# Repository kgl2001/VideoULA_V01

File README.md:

# VideoULA V01 — BBC Micro Video ULA Replacement
## 44-pin Xilinx XC9572XL CPLD Version

This repository contains the hardware design and firmware for the VideoULA V01, a drop-in replacement for the VC2069 Video ULA (IC6) in the Acorn BBC Micro Model B.

---

## Project Overview

The original BBC Micro Video ULA (IC6) is a custom ASIC that is no longer manufactured. Failed or missing ULAs result in a non-functional machine. This project provides a modern replacement using a CPLD and a small external SRAM for palette storage.

There are three hardware versions of this replacement, each in a separate repository:

| Version | CPLD | Macrocells | Tool | Repository |
|---|---|---|---|---|
| **V01** | Xilinx XC9572XL-10-VQ44 | 72 | ISE 14.7 | This repo |
| V02 | Xilinx XC9572XL-10-VQ64 | 72 | ISE 14.7 | [VideoULA_V02](https://github.com/kgl2001/VideoULA_V02) |
| V03 | Atmel ATF1504AS-10AU44 | 64 | Quartus 13.0 SP1 | [VideoULA_V03](https://github.com/kgl2001/VideoULA_V03) |

All three versions share the same 28-pin DIP footprint as the original ULA and are pin-compatible with the BBC Micro motherboard.

---

## V01 Hardware

- **CPLD**: Xilinx XC9572XL-10-VQ44 (72 macrocells, 3.3V core, 5V tolerant I/O)
- **SRAM**: ISSI IS62C256AL-45TLI (32K×8, 5V, TSOP-28, 45ns) — only locations 0-15 and bits 0-3 used
- **Oscillator**: 48MHz SMD oscillator (3225 package, 5V) — for 48MHz operating mode only
- **LDO**: XC6206P332MR (SOT-23, 3.3V) — powers CPLD core

### Hardware Revisions

| Revision | Status | Changes |
|---|---|---|
| Rev01 | Built and tested | Initial release |
| Rev02 | PCB designed, not yet built | Added 47Ω series resistor and 74LVC1G17 Schmitt trigger buffer on CLK_IN; CPLD pin assignments updated |
| Rev03 | PCB designed, not yet built | Added 74LV6T17 to buffer all clock outputs (8/4/2/1MHz, CRTC) for Master 128 compatibility |
| Rev04 | PCB designed, not yet built | Repositioned JTAG header |

Note: Only Rev01 has been built and tested. Rev02 onwards incorporate improvements identified during Rev01 testing. The latest revision supersedes the earlier ones, which are kept for the historical record.

### CLK_IN Reliability Daughterboard

During testing of Rev01 on BBC Micro machines with the original 16MHz clock circuit, some machines showed reliability issues in 16MHz operating mode — particularly on cold startup. Investigation revealed that the BBC's 16MHz crystal oscillator circuit produces a noisy clock signal that the CPLD occasionally misinterprets as spurious edges, causing display glitches.

To address this without waiting for a new PCB revision, a small standalone buffer board was developed. This daughterboard:

- Plugs into the BBC Micro motherboard in place of the VideoULA V01
- The VideoULA V01 then plugs into the daughterboard
- Intercepts the 16MHz clock signal from the BBC motherboard
- Passes it through a 47Ω series resistor and 74HCT14E Schmitt trigger buffer before it reaches the CPLD
- Passes all other signals through unchanged

The 74HCT14E was chosen as a through-hole part for ease of hand soldering. Rev02+ PCB designs use the smaller surface-mount 74LVC1G17 in conjunction with a series resistor to achieve the same signal conditioning in a more compact form.

This fix was confirmed to resolve the cold startup reliability issues on affected machines. The improvement has been incorporated into Rev02 of the V01 PCB and all subsequent hardware versions.

The daughterboard design files are included in this repository.

---

## Firmware

The firmware is written in Verilog and built using Xilinx ISE 14.7.

### Operating Modes

Two firmware builds are required — one per operating mode. To switch modes, reprogram the CPLD with the appropriate `.jed` file. A solder bridge on the PCB selects whether the 48MHz oscillator or the BBC's 16MHz clock is connected to the CPLD clock input.

#### 48MHz Mode (recommended)
- Uses the onboard 48MHz oscillator as the master clock
- Generates all BBC clock outputs (8/4/2/1MHz, CRTC, 6MHz) internally
- Provides clean, phase-locked 6MHz output for the SAA5050 teletext chip (tD ≈ 20ns ✓)
- Works reliably on all machines from cold power-up, including those with noisy clock circuits
- Build: uncomment `` `define CLK_48MHZ `` in `VideoULA.v`

#### 16MHz Mode
- Uses the BBC motherboard's 16MHz clock as the master clock
- No onboard oscillator required
- May show brief display noise on cold startup on machines with noisy 16MHz clock circuits
- The CLK_IN daughterboard resolves this on Rev01; Rev02+ has the fix built in
- The CPLD generates a phase-locked 6MHz from the 16MHz clock (small fixed jitter, about 10ns); the motherboard's own 6MHz can be used instead
- Build: uncomment `` `define CLK_16MHZ `` in `VideoULA.v`

#### CLK_AUTO (experimental)
- A third option, for the unified Rev02 to Rev04 boards, where the mode is read at power-up from the `SRAM_nWE` pin (JP2). One build covers both clocks
- Only tested on Rev01 hardware. It fits with no headroom (70 to 72 of 72 macrocells), and because the strap is read at power-up it may occasionally pick the wrong mode; power-cycle to recover
- The fixed 48MHz and 16MHz builds are smaller and have had more testing
- Build: uncomment `` `define CLK_AUTO `` (and comment out `CLK_48MHZ`) in `VideoULA.v`

### ISE Fitter Settings (critical)

| Setting | Value | Notes |
|---|---|---|
| Implementation Template | **Optimise Speed** | Density causes timing failures at temperature |
| Macrocell Power | **Std** | Low Power prevents BBC from booting |
| Output Slew Rate | Fast | |
| Default Powerup Value | Low | |
| Pterms | **14** (16MHz build only) | Default 25 causes silent fit failure in 16MHz build |

### Build Instructions

1. Open Xilinx ISE 14.7
2. Create a new project targeting `XC9572XL-10-VQ44`
3. Add `src/VideoULA.v` and `src/VideoULA.ucf` to the project
4. Select the operating mode by uncommenting the appropriate `define` in `VideoULA.v`
5. Set fitter options as above
6. Run `Implement Design` to generate the `.jed` file
7. Program the CPLD using iMPACT or a compatible JTAG programmer

---

## SRAM Wiring

The external SRAM stores the 16-entry colour palette (4 bits per entry):

| SRAM Pin | Connection |
|---|---|
| A0-A3 | CPLD SRAM_ADDR[0:3] |
| A4-A14 | GND (tie low) |
| D0-D3 | CPLD SRAM_DATA[0:3] (bidirectional) |
| D4-D7 | Leave unconnected |
| /WE | CPLD SRAM_nWE |
| /OE | GND (always output enabled) |
| /CS | GND (always selected) |

---

## 6MHz Clock for Mode 7 (Teletext)

The SAA5050 teletext chip requires a 6MHz clock with a specific phase relationship to the 1MHz system clock (tD = 6-60ns from 6MHz rising edge to 1MHz falling edge).

- **48MHz mode**: The CPLD generates a clean, phase-locked 6MHz output on the CLK_6M pin (tD ≈ 20ns ✓). This can be connected to the SAA5050 using a small replacement board for IC37 (Model B) or IC25 (Master) - see the [6MHz Interface Boards](https://github.com/kgl2001/VideoULA_V01/tree/main/KiCAD%20Files/6MHz%20Interface%20Boards).
- **16MHz mode**: The CPLD also generates a 6MHz output on CLK_6M, derived from the 16MHz clock and phase-locked to the 1MHz (tD ≈ 31ns ✓). It has a small fixed jitter (about 10ns), so M7CALIB can show slightly more noise. If CLK_6M is not connected, the BBC motherboard's existing 6MHz circuit is used as normal.

The CPLD's CLK_6M output is brought out on a single-pin header on the V01 board, marked **6MHz Clk** on the silkscreen (J2 in the schematic). To use the CPLD's 6MHz in either the 48MHz or the 16MHz build, connect it to the pin marked **6MHz** on the IC37 / IC25 interface board (J1 pin 1 in the schematic; the other pin, marked HSyn, is not used), or to the teletext IC's 6MHz input with a clip lead as described above. If it is left unconnected, the motherboard's own 6MHz is used as normal.

With the motherboard's own 6MHz circuit, the mode 7 cursor on a Master 128 is half a pixel (one column) to the left. The full Master 128 results are in the [CPLD README](CPLD%20Files/README.md#master-128-results-v01-rev01).

---

## PCB Design Notes

The PCB has been designed using KiCAD V10 as a 2-layer board. It can easily be changed to a 4-layer board with GND/Power planes on the inner layers if signal integrity is a concern.

### JLCPCB Fabrication

The board design includes a 5×5mm silkscreen box on the underside of the PCB. This is used by JLCPCB to position a QR code serial number. When ordering from JLCPCB:

- Select **Specify position** in the QR code / 2D barcode options during the ordering process
- If this option is not selected, JLCPCB will print the 5×5mm silkscreen box as-is and attempt to place the QR code at a different location of their choosing

If not using JLCPCB, the chosen fabricator will likely print the 5×5mm box as a plain white square on the PCB. To avoid this, remove the silkscreen box from the PCB design and regenerate the Gerber files before submitting.

### Assembly

A combined CPL (Component Placement List) and BOM (Bill of Materials) Excel file is included in the Gerbers folder. This can be used directly with the JLCPCB PCBA (PCB Assembly) service.

Note that the JLCPCB Economy PCBA process only assembles components on one side of the PCB. Select the **top side** for assembly — this leaves only the SRAM and its associated decoupling capacitor to be hand soldered to the underside of the board.

---

## Known Limitations

- **Cold startup noise (16MHz mode, standard clock machines)**: Machines with noisy 16MHz clock circuits may show brief display noise on cold power-up. Use the CLK_IN daughterboard (Rev01) or upgrade to Rev02+ which has the fix built in. The 48MHz operating mode is not affected.
- **Master 128 compatibility**: Rev01 has been tested on a Master 128 in both builds (see the [CPLD README](CPLD%20Files/README.md#master-128-results-v01-rev01)). Clock output buffering (added in Rev03) may still be required for full Master 128 compatibility on some machines.
- **SCART/HDMI adapter compatibility**: Some SCART→HDMI display adapters may show minor pixel artefacts with non-standard screen modes. RGBtoHDMI and direct CRT connections are not affected.

---

## Compatibility

Tested on BBC Micro Model B with original clock circuit and with clock fixer modification, and on a BBC Master 128 (Rev01).

---

## Credits

- **Ken Lowe** — PCB design, Verilog development and testing
- **hoglet (Stardot forums)** — Clock architecture analysis, DRAM timing analysis, SRAM write address setup analysis and proposed fix, community testing
- **radiofan (Stardot forums)** — SRAM write fix, 16MHz-derived 6MHz clock approach
- **Stardot community** — Testing, feedback and suggestions

---

## Licence

Hardware: [Creative Commons BY-SA 4.0](https://creativecommons.org/licenses/by-sa/4.0/)

Firmware: [MIT Licence](https://opensource.org/licenses/MIT)

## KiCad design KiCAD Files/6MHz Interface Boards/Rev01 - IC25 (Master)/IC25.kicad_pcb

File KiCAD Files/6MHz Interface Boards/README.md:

# 6MHz Interface Boards

Two small drop-in replacement boards that let the VideoULA CPLD supply the 6MHz clock to the SAA5050 teletext chip on a BBC Micro.

| Board | Fits | Replaces | Folder |
|---|---|---|---|
| IC37 board | BBC Model B | IC37 (74LS04) | [Rev01 - IC37 (Model B)](Rev01%20-%20IC37%20(Model%20B)) |
| IC25 board | BBC Master 128 | IC25 (74LS86) | [Rev01 - IC25 (Master)](Rev01%20-%20IC25%20(Master)) |

## Why these boards exist

In 48MHz mode the CPLD generates a clean 6MHz clock, phase-locked to the other video clocks (CLK_6M). Mode 7 gives its cleanest picture, and a correctly aligned cursor on both Model B and Master, when that clock is fed to the teletext IC instead of the motherboard's own 6MHz circuit.

The motherboard generates its 6MHz in the last gate of IC37 (Model B, pin 8) or IC25 (Master, pin 11). Each board replaces the original chip with a socketed 74HCT part, and lets you disconnect that final gate from the motherboard's 6MHz line and drive the line from the CPLD instead.

The boards are only needed to use the CPLD's CLK_6M. Without them the motherboard's own 6MHz circuit is used, as normal.

## Parts

The originals are 74LS parts, so the boards use **74HCT** parts, which run from 5V with TTL-compatible inputs. Do not substitute 3.3V logic (74LVC and similar).

| Board | Part | Package | JLCPCB |
|---|---|---|---|
| IC37 | 74HCT04 | TSSOP-14 | C131317 |
| IC25 | 74HCT86 | TSSOP-14 | C842458 |
| IC37 | 100nF decoupling capacitor (C37) | 0603 | C14663 |
| IC25 | 100nF decoupling capacitor (C25) | 0603 | C14663 |

The JLCPCB BOM covers only the SMD parts (the HCT chip and the capacitor). The through-hole parts are **not** in the BOM and must be fitted by hand:

- Two 7-pin round (machined) pin headers, soldered into the board's DIP pin positions. These plug into the motherboard socket.
- The 2-pin right-angle header J1, on the underside.

## Solder bridge settings

Both boards (IC37 and IC25) have two 3-pad solder bridges, JP1 and JP2, on the underside of the PCB, with identical settings. They are bridged 1-2 as shipped (the default). To change position, cut the thin track between pads 1 and 2 and bridge the pads you want with solder.

| Setting | JP1 | JP2 |
|---|---|---|
| **VideoULA 6MHz (default)**: CPLD drives the 6MHz line | bridge 1-2 | bridge 1-2 |
| **Inverted VideoULA 6MHz**: CPLD clock, inverted by the on-board gate | bridge 1-2 | bridge 2-3 |
| **Original 6MHz**: the motherboard's own circuit, as if the original chip were fitted | bridge 2-3 | bridge 2-3 |

For the default, the on-board gate is disconnected from the motherboard, and its input is tied to the CPLD clock so it does not float.

On the IC25 board the gate is an XOR with one input tied to 5V on the Master motherboard, so it acts as an inverter, just as the IC37 gate does.

## Connecting the CPLD

J1 is a 2-pin right-angle header fitted on the underside of the PCB. The labels are printed on the top silkscreen:

| J1 pin | Label | Use |
|---|---|---|
| 1 | 6MHz | Connect to the CPLD ULA's CLK_6M output |
| 2 | HSync | Added to aid testing; not needed in operation. Leave unconnected. (Silkscreen reads "HSyn" as there was no room for the full name.) |

## Fitting

1. Desolder the original chip (IC37 on a Model B, IC25 on a Master) from the motherboard, and fit a 14-pin DIP socket in its place. Note the orientation (pin 1).
2. Solder the round pin headers to the board, then plug the board into the socket, pin 1 matching.
3. Check the solder bridges (default is the VideoULA 6MHz).
4. Connect J1 to the CPLD ULA's CLK_6M.
5. Build the CPLD in either the 48MHz or the 16MHz mode (see the firmware READMEs).

### Without removing the chip

If you would rather not remove IC37 / IC25, you can cut the output leg of the gate that drives the 6MHz signal (pin 8 of IC37 on a Model B, pin 11 of IC25 on a Master) and connect the CPLD's CLK_6M to the teletext IC's 6MHz input with a clip lead (pin 19 of IC5 on a Model B, pin 19 of IC32 on a Master). Cutting the leg is a permanent modification to the chip.

## Status

Rev 01 has been built and tested in both the IC37 (Model B) and IC25 (Master) versions, on a Model B and a Master 128.

The 48MHz build gives the cleanest 6MHz. The 16MHz build now also works with the CPLD's 6MHz: it is generated from the 16MHz clock and phase-locked to the 1MHz clock. It has a small fixed jitter (about 10ns), so M7CALIB can show slightly more noise than in the 48MHz build. (An earlier 16MHz build generated the 6MHz from the 48MHz oscillator and could not be phase-locked to the 16MHz clock.)

## Files

Each folder is a KiCAD project (KiCAD 10) with schematic, PCB, a `3DModels` folder, and `Gerbers` for JLCPCB fabrication. The 3D model path is relative to the project, so keep the folder structure intact.

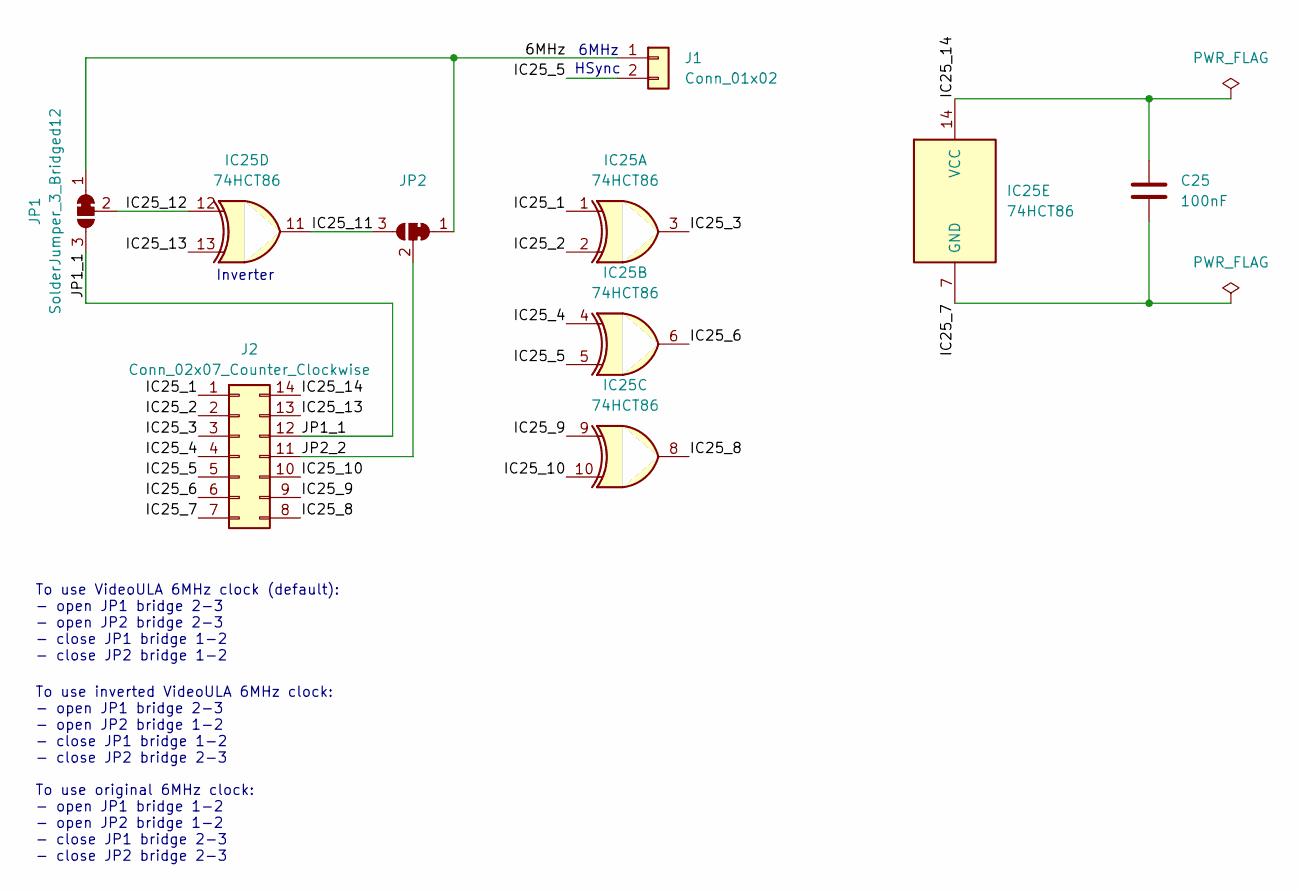
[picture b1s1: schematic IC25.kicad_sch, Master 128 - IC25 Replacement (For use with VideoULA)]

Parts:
C25: 100nF; C_0603_1608Metric
IC25: 74HCT86; TSSOP-14_4.4x5mm_P0.65mm
J1: Conn_01x02; PinHeader_1x02_P2.54mm_Horizontal
J2: Conn_02x07_Counter_Clockwise; DIP-14_W7.62mm
JP1, JP2: SolderJumper_3_Bridged12; SolderJumper-3_P1.3mm_Bridged12_RoundedPad1.0x1.5mm

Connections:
/6MHz: J1.1, JP1.1 (A), JP2.1 (A)
/IC25_1: IC25.1, J2.1
/IC25_2: IC25.2, J2.2
/IC25_3: IC25.3, J2.3
/IC25_4: IC25.4, J2.4
/IC25_5: IC25.5, J1.2, J2.5
/IC25_6: IC25.6, J2.6
/IC25_7: C25.2, IC25.7 (GND), J2.7
/IC25_8: IC25.8, J2.8
/IC25_9: IC25.9, J2.9
/IC25_10: IC25.10, J2.10
/IC25_11: IC25.11, JP2.3 (B)
/IC25_12: IC25.12, JP1.2 (C)
/IC25_13: IC25.13, J2.13
/IC25_14: C25.1, IC25.14 (VCC), J2.14
/JP1_1: J2.12, JP1.3 (B)
/JP2_2: J2.11, JP2.2 (C)

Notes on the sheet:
HSync
To use VideoULA 6MHz clock (default): - open JP1 bridge 2-3 - open JP2 bridge 2-3 - close JP1 bridge 1-2 - close JP2 bridge 1-2
To use inverted VideoULA 6MHz clock: - open JP1 bridge 2-3 - open JP2 bridge 1-2 - close JP1 bridge 1-2 - close JP2 bridge 2-3
6MHz
Inverter
To use original 6MHz clock: - open JP1 bridge 1-2 - open JP2 bridge 1-2 - close JP1 bridge 2-3 - close JP2 bridge 2-3

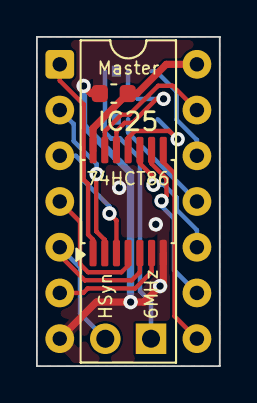
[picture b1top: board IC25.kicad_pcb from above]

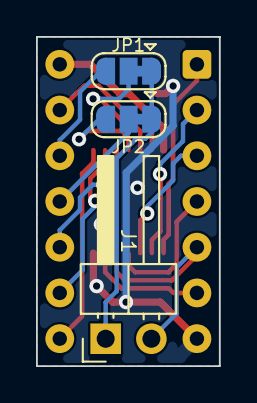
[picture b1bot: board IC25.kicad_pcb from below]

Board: 2 copper layers, 10.2 x 18.3 mm, 6 parts (3 on the bottom side), 17 nets.

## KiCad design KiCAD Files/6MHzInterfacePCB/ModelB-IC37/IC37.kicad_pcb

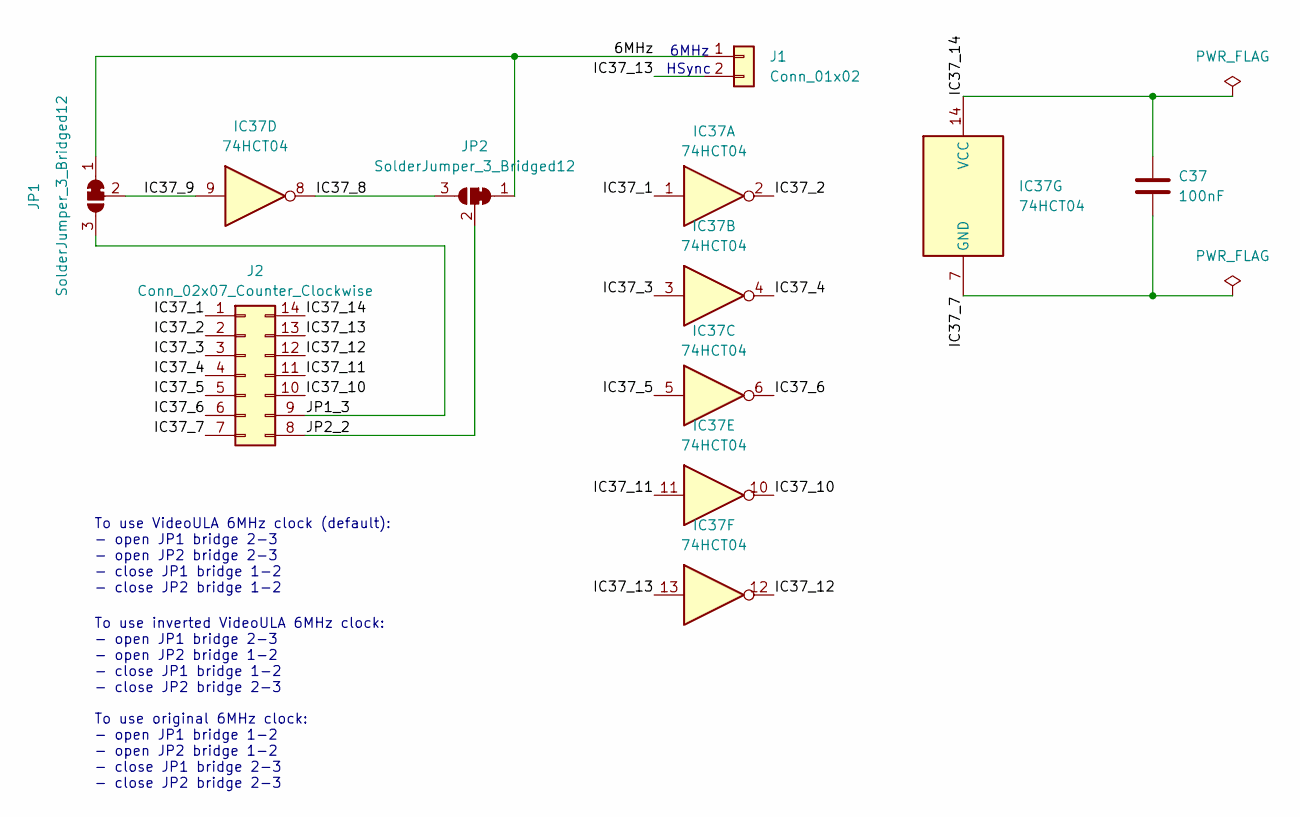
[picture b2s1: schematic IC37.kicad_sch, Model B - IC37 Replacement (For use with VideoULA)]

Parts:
C37: 100nF; C_0603_1608Metric
IC37: 74HCT04; TSSOP-14_4.4x5mm_P0.65mm
J1: Conn_01x02; PinHeader_1x02_P2.54mm_Horizontal
J2: Conn_02x07_Counter_Clockwise; DIP-14_W7.62mm
JP1, JP2: SolderJumper_3_Bridged12; SolderJumper-3_P1.3mm_Bridged12_RoundedPad1.0x1.5mm

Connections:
/6MHz: J1.1, JP1.1 (A), JP2.1 (A)
/IC37_1: IC37.1, J2.1
/IC37_2: IC37.2, J2.2
/IC37_3: IC37.3, J2.3
/IC37_4: IC37.4, J2.4
/IC37_5: IC37.5, J2.5
/IC37_6: IC37.6, J2.6
/IC37_7: C37.2, IC37.7 (GND), J2.7
/IC37_8: IC37.8, JP2.3 (B)
/IC37_9: IC37.9, JP1.2 (C)
/IC37_10: IC37.10, J2.10
/IC37_11: IC37.11, J2.11
/IC37_12: IC37.12, J2.12
/IC37_13: IC37.13, J1.2, J2.13
/IC37_14: C37.1, IC37.14 (VCC), J2.14
/JP1_3: J2.9, JP1.3 (B)
/JP2_2: J2.8, JP2.2 (C)

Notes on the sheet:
HSync
To use inverted VideoULA 6MHz clock: - open JP1 bridge 2-3 - open JP2 bridge 1-2 - close JP1 bridge 1-2 - close JP2 bridge 2-3
6MHz
To use original 6MHz clock: - open JP1 bridge 1-2 - open JP2 bridge 1-2 - close JP1 bridge 2-3 - close JP2 bridge 2-3
To use VideoULA 6MHz clock (default): - open JP1 bridge 2-3 - open JP2 bridge 2-3 - close JP1 bridge 1-2 - close JP2 bridge 1-2

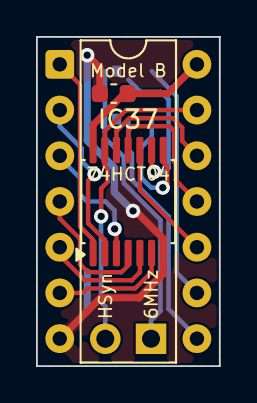
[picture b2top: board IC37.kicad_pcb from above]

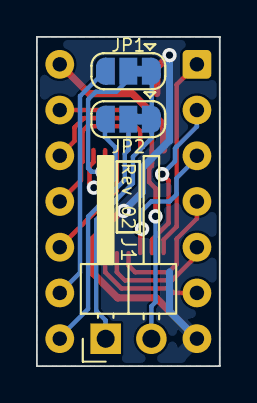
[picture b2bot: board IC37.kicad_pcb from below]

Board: 2 copper layers, 10.2 x 18.3 mm, 6 parts (3 on the bottom side), 17 nets.

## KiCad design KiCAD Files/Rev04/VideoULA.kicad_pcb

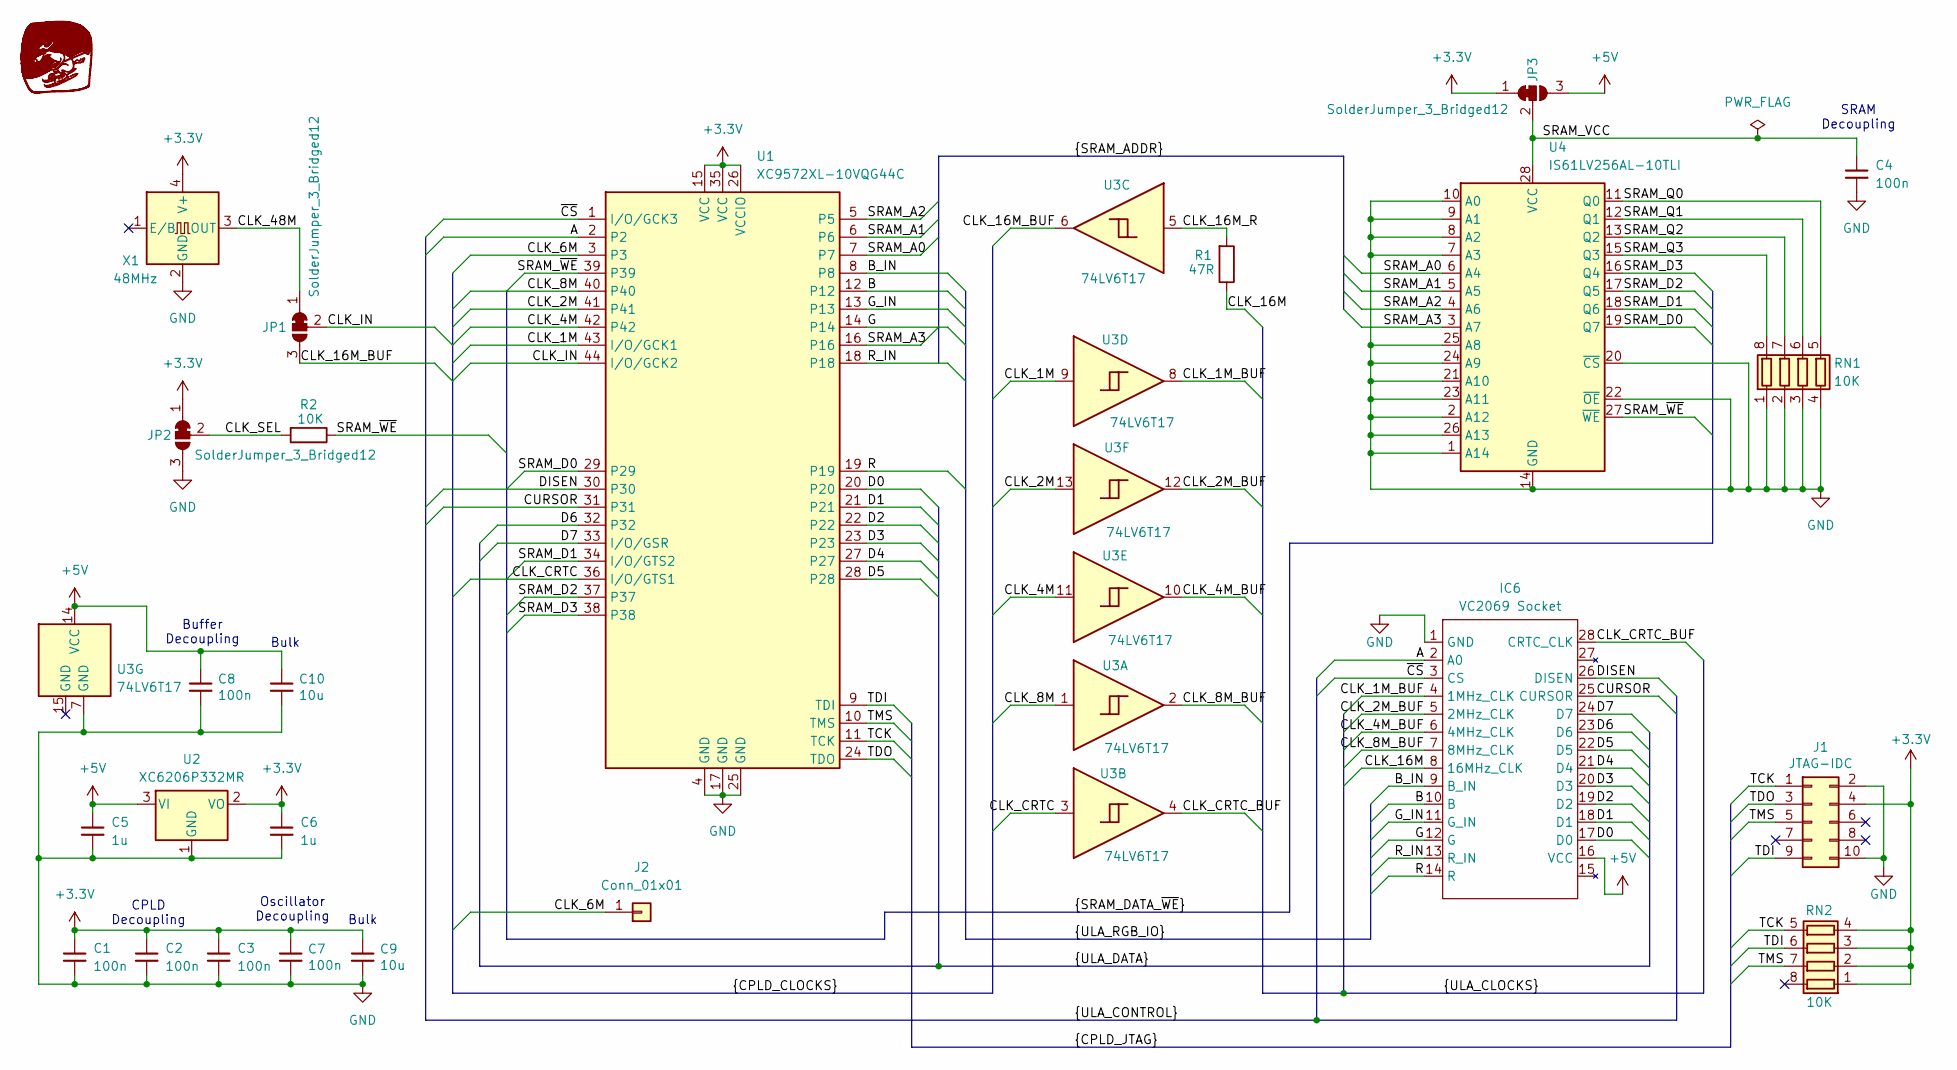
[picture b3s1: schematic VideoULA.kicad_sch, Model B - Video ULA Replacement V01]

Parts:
C1, C2, C3, C4, C7, C8: 100n; C_0603_1608Metric; JLC Part Number C14663
C5, C6: 1u; C_0603_1608Metric; JLC Part Number C15849
C9, C10: 10u; C_0603_1608Metric; JLC Part Number C19702
G1: Skidog; skidog_inv
IC6: VC2069 Socket; DIP-28_W15.24mm
J1: JTAG-IDC; PinHeader_2x05_P2.54mm_Vertical
J2: Conn_01x01; PinHeader_1x01_P2.54mm_Horizontal
JP1, JP2, JP3: SolderJumper_3_Bridged12; SolderJumper-3_P1.3mm_Bridged12_RoundedPad1.0x1.5mm
R1: 47R; R_0603_1608Metric; JLC Part Number C23182
R2: 10K; R_0603_1608Metric; JLC Part Number C25804
RN1, RN2: 10K; R_Array_Convex_4x0603; JLC Part Number C29718
U1: XC9572XL-10VQG44C; LQFP-44_10x10mm_P0.8mm; JLC Part Number C569042
U2: XC6206P332MR; SOT-23-3; JLC Part Number C5446
U3: 74LV6T17; DHWQFN-14-1EP_2.5x3mm_P0.5mm_EP1x1.5mm_ThermalVias; JLC Part Number C22428345
U4: IS61LV256AL-10TLI; TSOP-I-28_11.8x8mm_P0.55mm_SRAM; JLC Part Number C2062662
X1: 48MHz; Oscillator_SMD_Yajingxin_TFOM48M4RHKCNT2T-4Pin_3.2x2.5mm; JLC Part Number C454614

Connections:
+3.3V: C1.1, C2.1, C3.1, C6.1, C7.1, C9.1, J1.4, JP2.1 (A), JP3.1 (A), RN2.1 (R1.1), RN2.2 (R2.1), RN2.3 (R3.1), RN2.4 (R4.1), U1.15 (VCC), U1.26 (VCCIO), U1.35 (VCC), U2.2 (VO), X1.4 (V+)
+5V: C5.1, C8.1, C10.1, IC6.16 (VCC), JP3.3 (B), U2.3 (VI), U3.14 (VCC)
/A: IC6.2 (A0), U1.2
/B: IC6.10 (B), U1.12
/B_IN: IC6.9 (B_IN), U1.8
/CLK_1M: U1.43 (I/O/GCK1), U3.9
/CLK_1M_BUF: IC6.4 (1MHz_CLK), U3.8
/CLK_2M: U1.41, U3.13
/CLK_2M_BUF: IC6.5 (2MHz_CLK), U3.12
/CLK_4M: U1.42, U3.11
/CLK_4M_BUF: IC6.6 (4MHz_CLK), U3.10
/CLK_6M: J2.1 (Pin_1_1), U1.3
/CLK_8M: U1.40, U3.1
/CLK_8M_BUF: IC6.7 (8MHz_CLK), U3.2
/CLK_16M: IC6.8 (16MHz_CLK), R1.1
/CLK_16M_BUF: JP1.3 (B), U3.6
/CLK_16M_R: R1.2, U3.5
/CLK_48M: JP1.1 (A), X1.3 (OUT)
/CLK_CRTC: U1.36 (I/O/GTS1), U3.3
/CLK_CRTC_BUF: IC6.28 (CRTC_CLK), U3.4
/CLK_IN: JP1.2 (C), U1.44 (I/O/GCK2)
/CLK_SEL: JP2.2 (C), R2.2
/CURSOR: IC6.25 (CURSOR), U1.31
/D0: IC6.17 (D0), U1.20
/D1: IC6.18 (D1), U1.21
/D2: IC6.19 (D2), U1.22
/D3: IC6.20 (D3), U1.23
/D4: IC6.21 (D4), U1.27
/D5: IC6.22 (D5), U1.28
/D6: IC6.23 (D6), U1.32
/D7: IC6.24 (D7), U1.33 (I/O/GSR)
/DISEN: IC6.26 (DISEN), U1.30
/G: IC6.12 (G), U1.14
/G_IN: IC6.11 (G_IN), U1.13
/R: IC6.14 (R), U1.19
/R_IN: IC6.13 (R_IN), U1.18
/SRAM_A0: U1.7, U4.6 (A4)
/SRAM_A1: U1.6, U4.5 (A5)
/SRAM_A2: U1.5, U4.4 (A6)
/SRAM_A3: U1.16, U4.3 (A7)
/SRAM_D0: U1.29, U4.19 (Q7)
/SRAM_D1: U1.34 (I/O/GTS2), U4.18 (Q6)
/SRAM_D2: U1.37, U4.17 (Q5)
/SRAM_D3: U1.38, U4.16 (Q4)
/SRAM_Q0: RN1.5 (R4.2), U4.11 (Q0)
/SRAM_Q1: RN1.6 (R3.2), U4.12 (Q1)
/SRAM_Q2: RN1.7 (R2.2), U4.13 (Q2)
/SRAM_Q3: RN1.8 (R1.2), U4.15 (Q3)
/SRAM_VCC: C4.1, JP3.2 (C), U4.28 (VCC)
/SRAM_~WE: R2.1, U1.39, U4.27 (~WE)
/TCK: J1.1, RN2.5 (R4.2), U1.11 (TCK)
/TDI: J1.9, RN2.6 (R3.2), U1.9 (TDI)
/TDO: J1.3, U1.24 (TDO)
/TMS: J1.5, RN2.7 (R2.2), U1.10 (TMS)
/~CS: IC6.3 (CS), U1.1 (I/O/GCK3)
GND: C1.2, C2.2, C3.2, C4.2, C5.2, C6.2, C7.2, C8.2, C9.2, C10.2, IC6.1 (GND), J1.2, J1.10, JP2.3 (B), RN1.1 (R1.1), RN1.2 (R2.1), RN1.3 (R3.1), RN1.4 (R4.1), U1.4 (GND), U1.17 (GND), U1.25 (GND), U2.1 (GND), U3.7 (GND), U4.1 (A14), U4.2 (A12), U4.7 (A3), U4.8 (A2), U4.9 (A1), U4.10 (A0), U4.14 (GND), U4.20 (~CS), U4.21 (A10), U4.22 (~OE), U4.23 (A11), U4.24 (A9), U4.25 (A8), U4.26 (A13), X1.2 (GND)

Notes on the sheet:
SRAM Decoupling
Oscillator Decoupling
CPLD Decoupling
Bulk
Buffer Decoupling

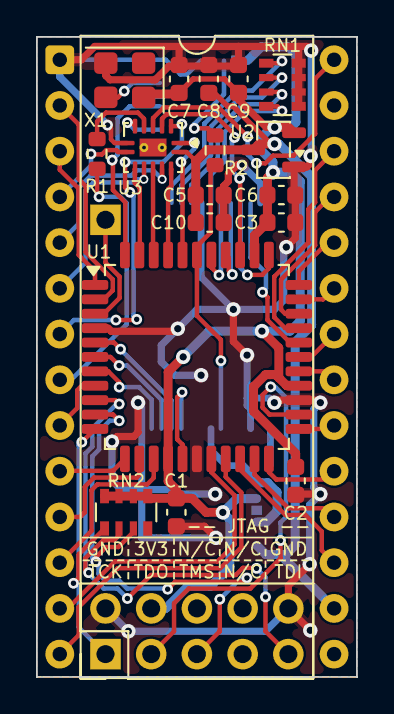
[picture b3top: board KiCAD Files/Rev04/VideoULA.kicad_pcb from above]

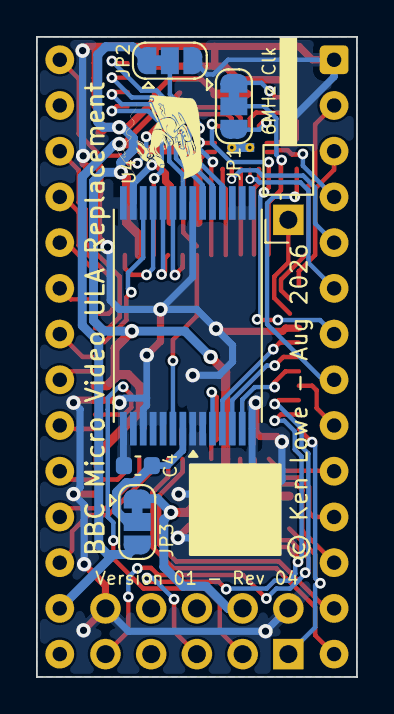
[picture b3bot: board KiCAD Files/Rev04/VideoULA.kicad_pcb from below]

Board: 2 copper layers, 17.8 x 35.6 mm, 26 parts (7 on the bottom side), 56 nets.

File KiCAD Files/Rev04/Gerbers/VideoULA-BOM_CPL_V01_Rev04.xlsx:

Designator | Val | Package | Mid X | Mid Y | Rotation | Layer | JLC Part Number
C4 | 100n | C_0603_1608Metric | 88.882531999999998 | -62.421548000000001 | 0 | bottom | C14663
U4 | IS61LV256AL-10TLI | TSOP-I-28_11.8x8mm_P0.55mm_SRAM | 86.111000000000004 | -54.097000000000001 | 90 | bottom | C2062662
C1 | 100n | C_0603_1608Metric | 84.46 | -65.013999999999996 | -90 | top | C14663
C2 | 100n | C_0603_1608Metric | 91.089731999999998 | -63.266348000000001 | -90 | top | C14663
C3 | 100n | C_0603_1608Metric | 90.293999999999997 | -48.915399999999998 | 0 | top | C14663
C5 | 1u | C_0603_1608Metric | 86.3142 | -47.391399999999997 | 0 | top | C15849
C6 | 1u | C_0603_1608Metric | 90.293999999999997 | -47.391399999999997 | 0 | top | C15849
C7 | 100n | C_0603_1608Metric | 84.612399999999994 | -40.939799999999998 | 90 | top | C14663
C8 | 100n | C_0603_1608Metric | 86.2624 | -40.939799999999998 | 90 | top | C14663
C9 | 10u | C_0603_1608Metric | 87.912400000000005 | -40.939799999999998 | 90 | top | C19702
C10 | 10u | C_0603_1608Metric | 86.3142 | -48.915399999999998 | 0 | top | C19702
R1 | 47R | R_0603_1608Metric | 80.0578 | -45.105400000000003 | 90 | top | C23182
R2 | 10K | R_0603_1608Metric | 86.611000000000004 | -44.902200000000001 | 90 | top | C25804
RN1 | 10K | R_Array_Convex_4x0603 | 90.355732000000003 | -41.263348000000001 | -90 | top | C29718
RN2 | 10K | R_Array_Convex_4x0603 | 81.672399999999996 | -65.013999999999996 | 0 | top | C29718
U1 | XC9572XL-10VQG44C | LQFP-44_10x10mm_P0.8mm | 85.602999999999994 | -56.383000000000003 | -90 | top | C569042
U2 | XC6206P332MR | SOT-23-3 | 89.862200000000001 | -44.876800000000003 | 0 | top | C5446
U3 | 74LV6T17 | DHWQFN-14-1EP_2.5x3mm_P0.5mm_EP1x1.5mm_ThermalVias | 83.164599999999993 | -44.7498 | -90 | top | C22428345
X1 | 48MHz | Oscillator_SMD_Yajingxin_TFOM48M4RHKCNT2T-4Pin_3.2x2.5mm | 81.592731999999998 | -41.009348000000003 | 180 | top | C454614

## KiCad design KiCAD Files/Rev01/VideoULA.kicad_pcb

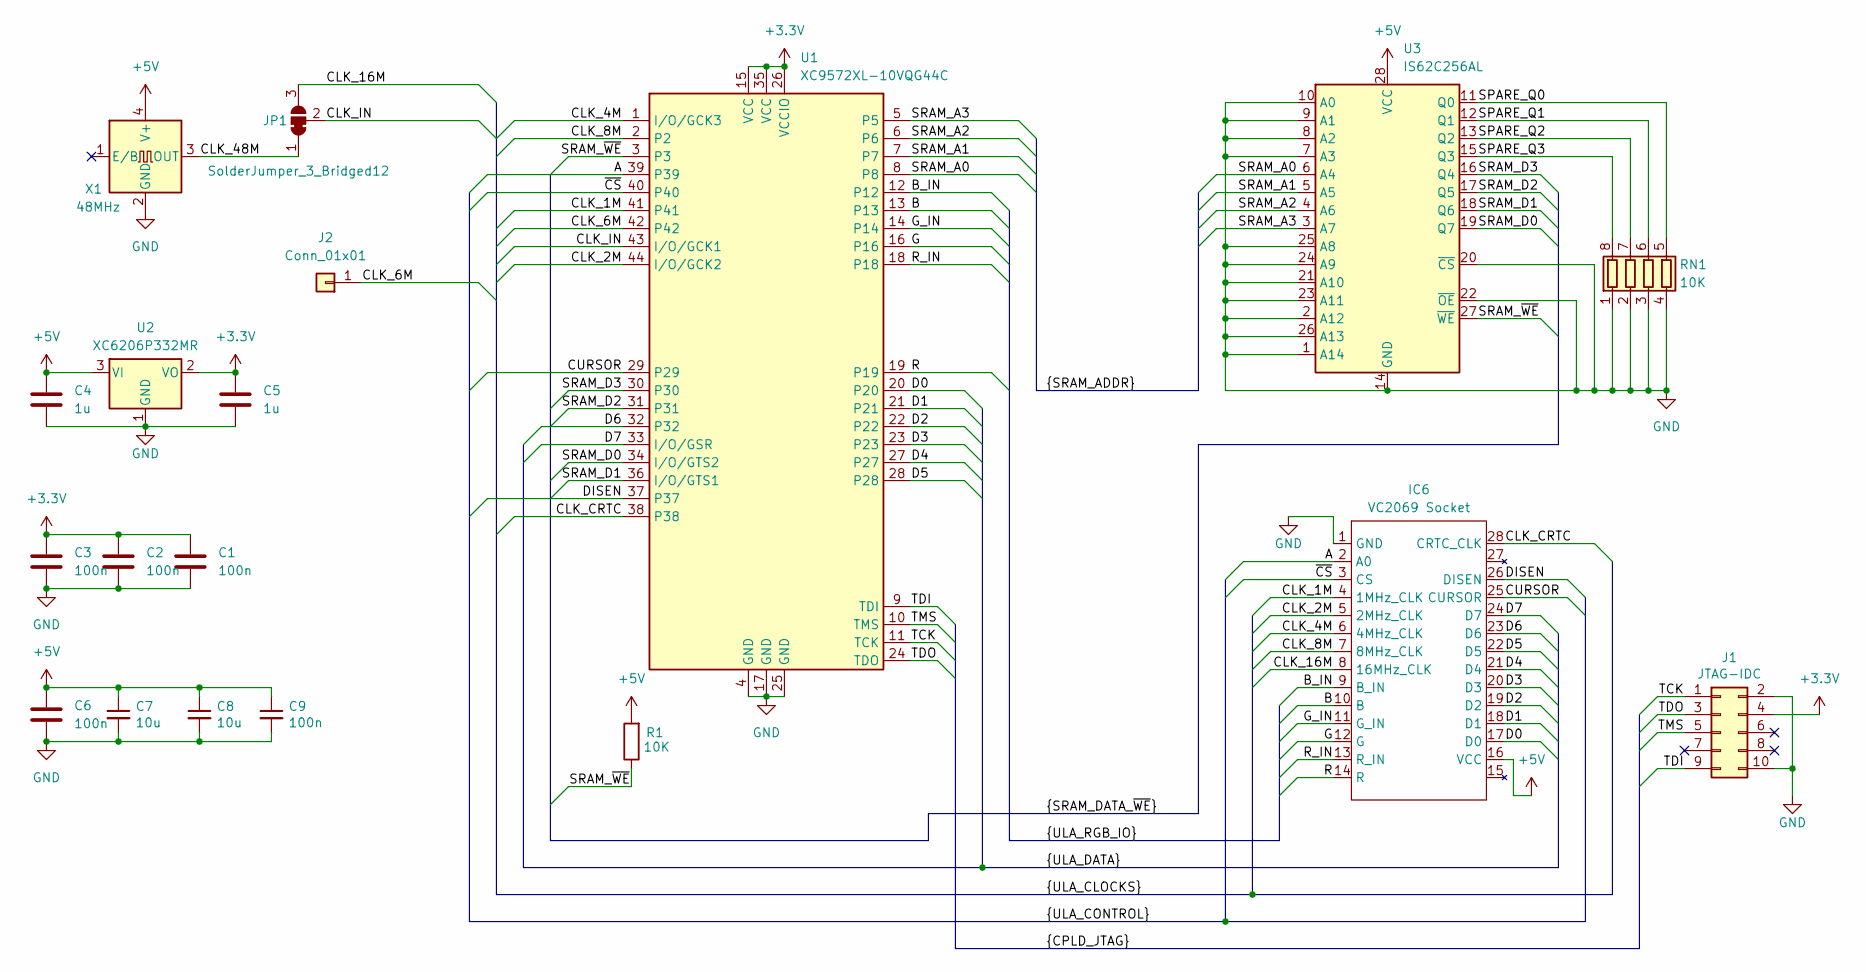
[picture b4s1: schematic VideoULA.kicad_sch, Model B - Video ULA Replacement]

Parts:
C1, C2, C3, C6, C9: 100n; C_0603_1608Metric; JLC Part Number C14663
C4, C5: 1u; C_0603_1608Metric; JLC Part Number C15849
C7, C8: 10u; C_0603_1608Metric; JLC Part Number C19702
IC6: VC2069 Socket; DIP-28_W15.24mm
J1: JTAG-IDC; PinHeader_2x05_P2.54mm_Vertical
J2: Conn_01x01; PinHeader_1x01_P2.54mm_Horizontal
JP1: SolderJumper_3_Bridged12; SolderJumper-3_P1.3mm_Bridged12_RoundedPad1.0x1.5mm
R1: 10K; R_0603_1608Metric; JLC Part Number C25804
RN1: 10K; R_Array_Convex_4x0603; JLC Part Number C29718
U1: XC9572XL-10VQG44C; LQFP-44_10x10mm_P0.8mm; JLC Part Number C569042
U2: XC6206P332MR; SOT-23-3; JLC Part Number C5446
U3: IS62C256AL; TSOP-I-28_11.8x8mm_P0.55mm_SRAM; JLC Part Number C47143
X1: 48MHz; Oscillator_SMD_Yajingxin_TFOM48M4RHKCNT2T-4Pin_3.2x2.5mm; JLC Part Number C454614

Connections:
+3.3V: C1.1, C2.1, C3.1, C5.1, J1.4, U1.15 (VCC), U1.26 (VCCIO), U1.35 (VCC), U2.2 (VO)
+5V: C4.1, C6.1, C7.1, C8.1, C9.1, IC6.16 (VCC), R1.2, U2.3 (VI), U3.28 (VCC), X1.4 (V+)
/A: IC6.2 (A0), U1.39
/B: IC6.10 (B), U1.13
/B_IN: IC6.9 (B_IN), U1.12
/CLK_1M: IC6.4 (1MHz_CLK), U1.41
/CLK_2M: IC6.5 (2MHz_CLK), U1.44 (I/O/GCK2)
/CLK_4M: IC6.6 (4MHz_CLK), U1.1 (I/O/GCK3)
/CLK_6M: J2.1 (Pin_1_1), U1.42
/CLK_8M: IC6.7 (8MHz_CLK), U1.2
/CLK_16M: IC6.8 (16MHz_CLK), JP1.3 (B)
/CLK_48M: JP1.1 (A), X1.3 (OUT)
/CLK_CRTC: IC6.28 (CRTC_CLK), U1.38
/CLK_IN: JP1.2 (C), U1.43 (I/O/GCK1)
/CURSOR: IC6.25 (CURSOR), U1.29
/D0: IC6.17 (D0), U1.20
/D1: IC6.18 (D1), U1.21
/D2: IC6.19 (D2), U1.22
/D3: IC6.20 (D3), U1.23
/D4: IC6.21 (D4), U1.27
/D5: IC6.22 (D5), U1.28
/D6: IC6.23 (D6), U1.32
/D7: IC6.24 (D7), U1.33 (I/O/GSR)
/DISEN: IC6.26 (DISEN), U1.37
/G: IC6.12 (G), U1.16
/G_IN: IC6.11 (G_IN), U1.14
/R: IC6.14 (R), U1.19
/R_IN: IC6.13 (R_IN), U1.18
/SPARE_Q0: RN1.5 (R4.2), U3.11 (Q0)
/SPARE_Q1: RN1.6 (R3.2), U3.12 (Q1)
/SPARE_Q2: RN1.7 (R2.2), U3.13 (Q2)
/SPARE_Q3: RN1.8 (R1.2), U3.15 (Q3)
/SRAM_A0: U1.8, U3.6 (A4)
/SRAM_A1: U1.7, U3.5 (A5)
/SRAM_A2: U1.6, U3.4 (A6)
/SRAM_A3: U1.5, U3.3 (A7)
/SRAM_D0: U1.34 (I/O/GTS2), U3.19 (Q7)
/SRAM_D1: U1.36 (I/O/GTS1), U3.18 (Q6)
/SRAM_D2: U1.31, U3.17 (Q5)
/SRAM_D3: U1.30, U3.16 (Q4)
/SRAM_~WE: R1.1, U1.3, U3.27 (~WE)
/TCK: J1.1, U1.11 (TCK)
/TDI: J1.9, U1.9 (TDI)
/TDO: J1.3, U1.24 (TDO)
/TMS: J1.5, U1.10 (TMS)
/~CS: IC6.3 (CS), U1.40
GND: C1.2, C2.2, C3.2, C4.2, C5.2, C6.2, C7.2, C8.2, C9.2, IC6.1 (GND), J1.2, J1.10, RN1.1 (R1.1), RN1.2 (R2.1), RN1.3 (R3.1), RN1.4 (R4.1), U1.4 (GND), U1.17 (GND), U1.25 (GND), U2.1 (GND), U3.1 (A14), U3.2 (A12), U3.7 (A3), U3.8 (A2), U3.9 (A1), U3.10 (A0), U3.14 (GND), U3.20 (~CS), U3.21 (A10), U3.22 (~OE), U3.23 (A11), U3.24 (A9), U3.25 (A8), U3.26 (A13), X1.2 (GND)

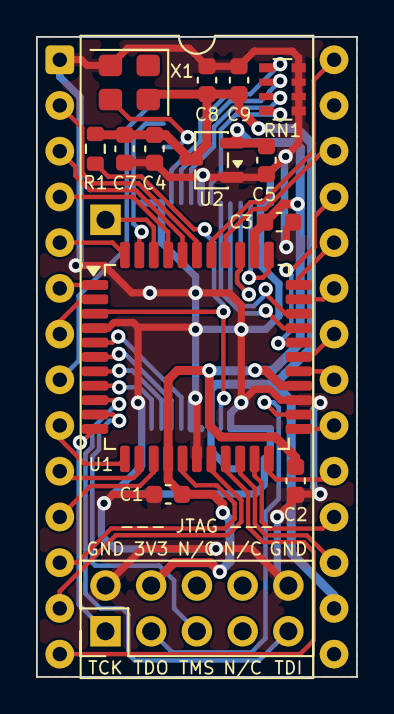
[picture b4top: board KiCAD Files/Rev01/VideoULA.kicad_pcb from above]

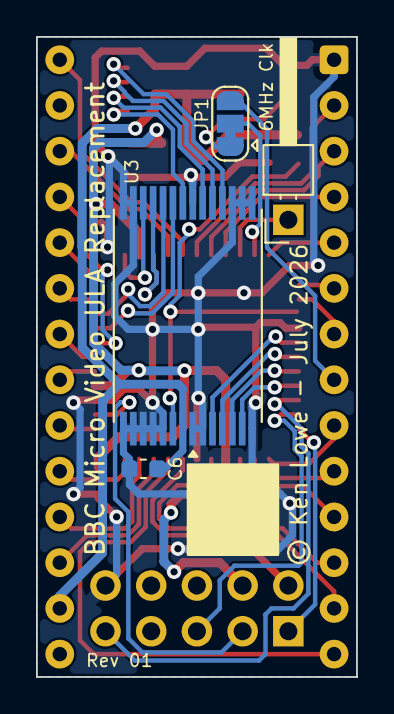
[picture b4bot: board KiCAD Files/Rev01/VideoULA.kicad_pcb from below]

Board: 2 copper layers, 17.8 x 35.6 mm, 19 parts (4 on the bottom side), 47 nets.

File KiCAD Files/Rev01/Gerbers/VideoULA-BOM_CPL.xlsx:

Designator | Val | Package | Mid X | Mid Y | Rotation | Layer | JLC Part Number
C6 | 100n | C_0603_1608Metric | 88.577731999999997 | -62.599347999999999 | 0 | bottom | C14663
U3 | IS62C256AL | TSOP-I-28_11.8x8mm_P0.55mm_SRAM | 86.111000000000004 | -54.097000000000001 | 90 | bottom | C47143
C1 | 100n | C_0603_1608Metric | 84.002799999999993 | -64.016347999999994 | 180 | top | C14663
C2 | 100n | C_0603_1608Metric | 91.089731999999998 | -63.266348000000001 | -90 | top | C14663
C3 | 100n | C_0603_1608Metric | 90.167000000000002 | -48.893999999999998 | 0 | top | C14663
C4 | 1u | C_0603_1608Metric | 83.243731999999994 | -44.819347999999998 | -90 | top | C15849
C5 | 1u | C_0603_1608Metric | 89.466731999999993 | -45.454348000000003 | -90 | top | C15849
C7 | 10n | C_0603_1608Metric | 81.584732000000002 | -44.819347999999998 | -90 | top | C57112
C8 | 10n | C_0603_1608Metric | 86.164732000000001 | -41.009348000000003 | 90 | top | C57112
C9 | 100n | C_0603_1608Metric | 87.942732000000007 | -41.009348000000003 | 90 | top | C14663
R1 | 10K | R_0603_1608Metric | 79.959131999999997 | -44.819347999999998 | 90 | top | C25804
RN1 | 10K | R_Array_Convex_4x0603 | 90.355732000000003 | -41.517347999999998 | 90 | top | C29718
U1 | XC9572XL-10VQG44C | LQFP-44_10x10mm_P0.8mm | 85.602999999999994 | -56.383000000000003 | 270 | top | C569042
U2 | XC6206P332MR | SOT-23-3 | 86.418732000000006 | -45.454348000000003 | 0 | top | C5446
X1 | 48MHz | Oscillator_SMD_Yajingxin_TFOM48M4RHKCNT2T-4Pin_3.2x2.5mm | 81.846732000000003 | -41.136347999999998 | 180 | top | C454614

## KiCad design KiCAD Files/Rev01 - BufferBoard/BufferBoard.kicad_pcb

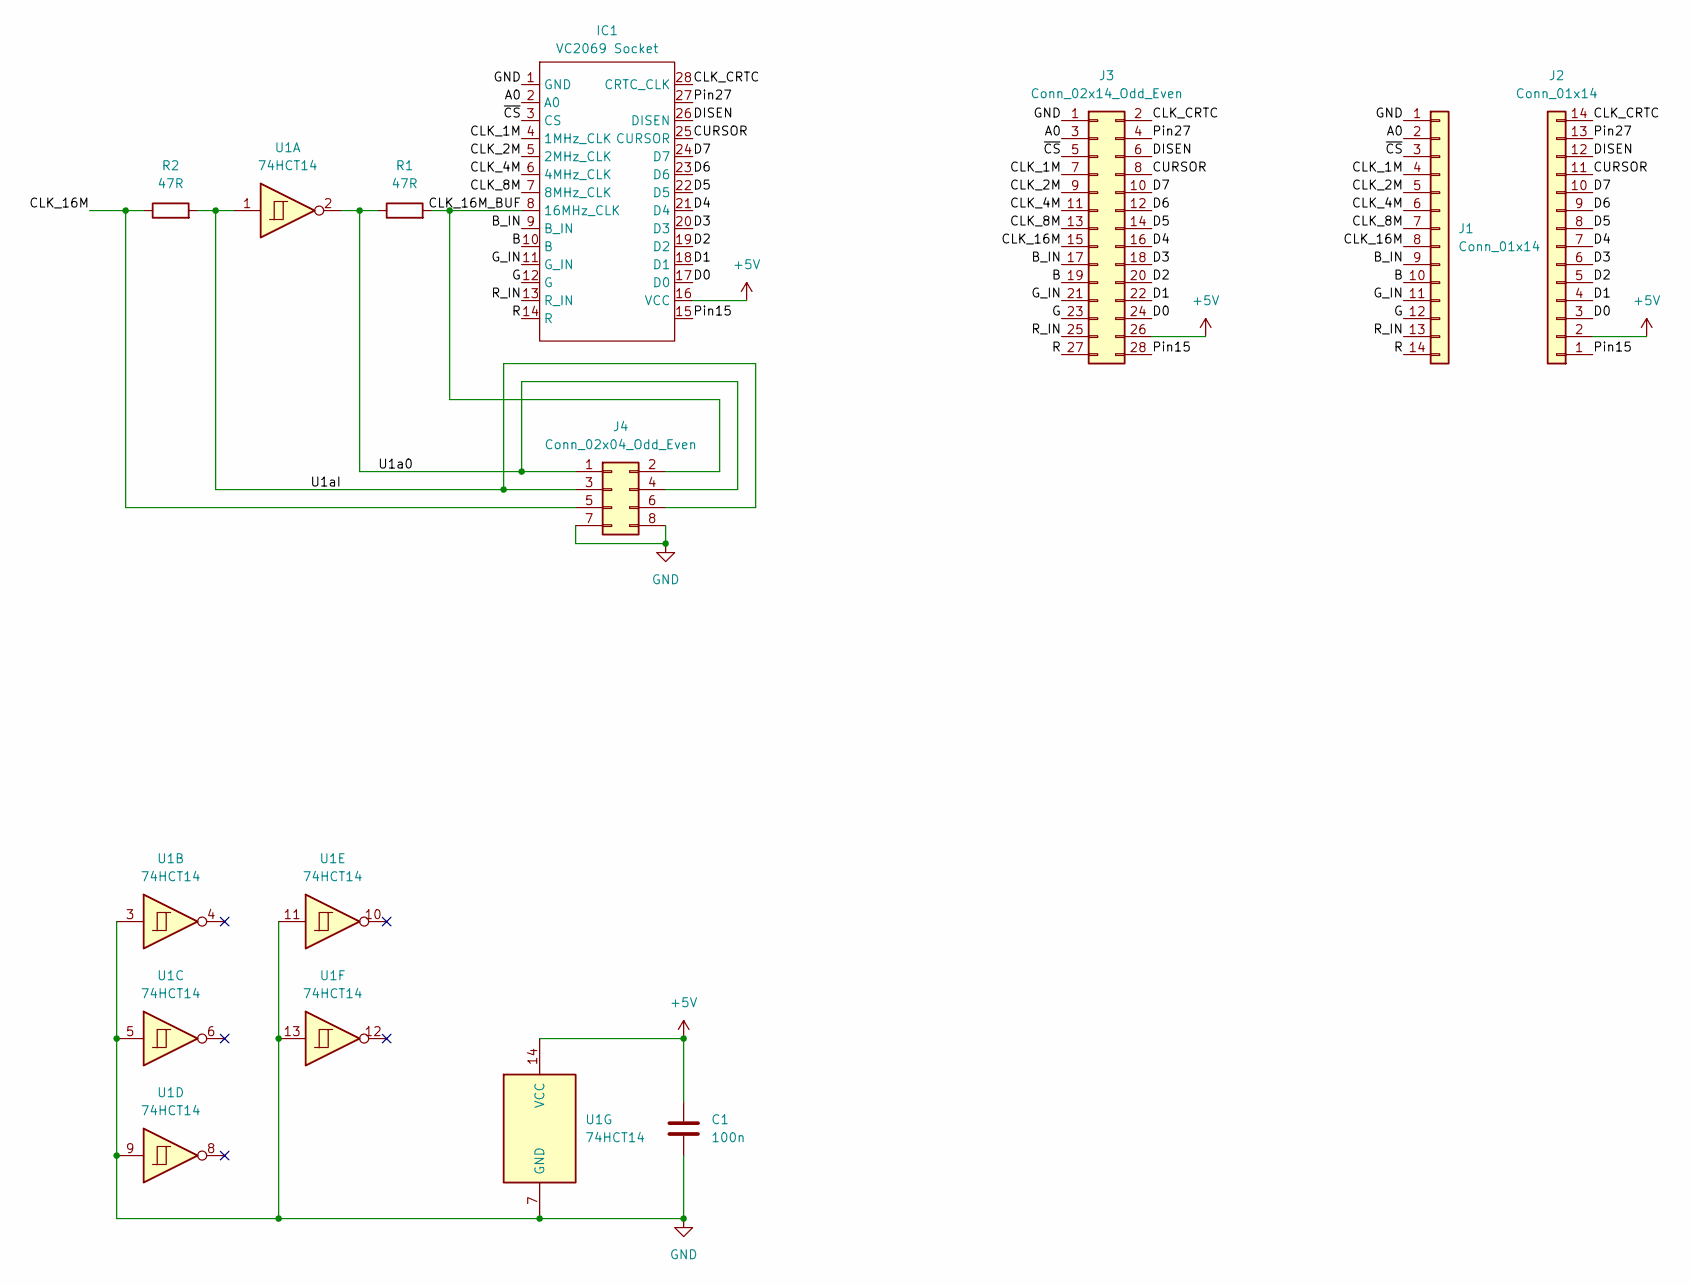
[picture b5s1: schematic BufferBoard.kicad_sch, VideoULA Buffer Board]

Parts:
C1: 100n; C_Disc_D4.3mm_W1.9mm_P5.00mm; JLC Part Number C14663
IC1: VC2069 Socket; DIP-28_W15.24mm_Socket
J1, J2: Conn_01x14; PinHeader_1x14_P2.54mm_Vertical
J3: Conn_02x14_Odd_Even; PinHeader_2x14_P2.54mm_Vertical
J4: Conn_02x04_Odd_Even; PinHeader_2x04_P2.54mm_Vertical
R1, R2: 47R; R_Axial_DIN0207_L6.3mm_D2.5mm_P10.16mm_Horizontal
U1: 74HCT14; DIP-14_W7.62mm_Socket

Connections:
+5V: C1.1, IC1.16 (VCC), J2.2, J3.26, U1.14 (VCC)
/A0: IC1.2 (A0), J1.2, J3.3
/B: IC1.10 (B), J1.10, J3.19
/B_IN: IC1.9 (B_IN), J1.9, J3.17
/CLK_1M: IC1.4 (1MHz_CLK), J1.4, J3.7
/CLK_2M: IC1.5 (2MHz_CLK), J1.5, J3.9
/CLK_4M: IC1.6 (4MHz_CLK), J1.6, J3.11
/CLK_8M: IC1.7 (8MHz_CLK), J1.7, J3.13
/CLK_16M: J1.8, J3.15, J4.5, R2.1
/CLK_16M_BUF: IC1.8 (16MHz_CLK), J4.2, R1.2
/CLK_CRTC: IC1.28 (CRTC_CLK), J2.14, J3.2
/CURSOR: IC1.25 (CURSOR), J2.11, J3.8
/D0: IC1.17 (D0), J2.3, J3.24
/D1: IC1.18 (D1), J2.4, J3.22
/D2: IC1.19 (D2), J2.5, J3.20
/D3: IC1.20 (D3), J2.6, J3.18
/D4: IC1.21 (D4), J2.7, J3.16
/D5: IC1.22 (D5), J2.8, J3.14
/D6: IC1.23 (D6), J2.9, J3.12
/D7: IC1.24 (D7), J2.10, J3.10
/DISEN: IC1.26 (DISEN), J2.12, J3.6
/G: IC1.12 (G), J1.12, J3.23
/G_IN: IC1.11 (G_IN), J1.11, J3.21
/Pin15: IC1.15, J2.1, J3.28
/Pin27: IC1.27, J2.13, J3.4
/R: IC1.14 (R), J1.14, J3.27
/R_IN: IC1.13 (R_IN), J1.13, J3.25
/U1a0: J4.1, J4.4, R1.1, U1.2
/U1aI: J4.3, J4.6, R2.2, U1.1
/~CS: IC1.3 (CS), J1.3, J3.5
GND: C1.2, IC1.1 (GND), J1.1, J3.1, J4.7, J4.8, U1.3, U1.5, U1.7 (GND), U1.9, U1.11, U1.13

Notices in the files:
KiCAD Files/Rev01 - BufferBoard/BufferBoard.kicad_pcb:
© Ken Lowe - Aug 2026
KiCAD Files/Rev01/VideoULA.kicad_pcb:
© Ken Lowe - July 2026
